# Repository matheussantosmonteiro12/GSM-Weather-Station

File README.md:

# GSM-Weather-Station
Estação meteorológica que mede microclimas e envia esses dados via GSM. 
## Resumo: 
Este projeto propõe uma rede de monitoramento climático utilizando estações meteorológicas autonomas, que transmitem os dados coletados atraves rede GSM (Global System for Mobile Communications), para um Middleware IoT, responsável por fazer a persistencia dos dados e fornecer informações sobre o clima para as diversas aplicações, focadas em ajudar os usuários no planejamento da rotina diária.
## Programas Necessários:
-**IDE arduino**, https://www.arduino.cc/en/Main/Software.

-**Cura Software** ou **Slic3r**.

## Companentes necessários:
- 1 Módulo A6 Gsm/Gprs.

- 1 Arduino mega.

- 1 Módulo sensor de chuva.

- 1 Módulo sensor de luminosidade de luz LDR.

- 1 Sensor de umidade e temperatura DHT 11.

- 1 Atiny 85.

- 1 Regulador de Tensão 7805 5V.

- 1 Relé nec 5V.

- 1 Módulo carregador tp4056.

- 3 Painel Placa Solar 12v 1.50w Carregador Ecologico 9v.

- 1 Modulo Conversor Tensão Dc/dc Step Up.

## Arquitetura da solução proposta:

## Circuito de alimentação:

**1) Relé, 2) Microcontrolador, 3) Carregador de bateria, 4) Regulador de tensão.**

## Circuito principal:

**1) Sensor de gás, 2) Sensor de temperatura e umidade, 3) Sensor de luminosidade, 4) Sensor de chuva, 5) A6 GSM/GPRS, 6) Microcontrolador.**

## Versão final da estação:

#### Link do Artigo sobre esse projeto:
https://ieeexplore.ieee.org/abstract/document/8896242

#### OBS:
Para qualquer outras duvidas me mande um email no matheus.monteiro@uiot.org.

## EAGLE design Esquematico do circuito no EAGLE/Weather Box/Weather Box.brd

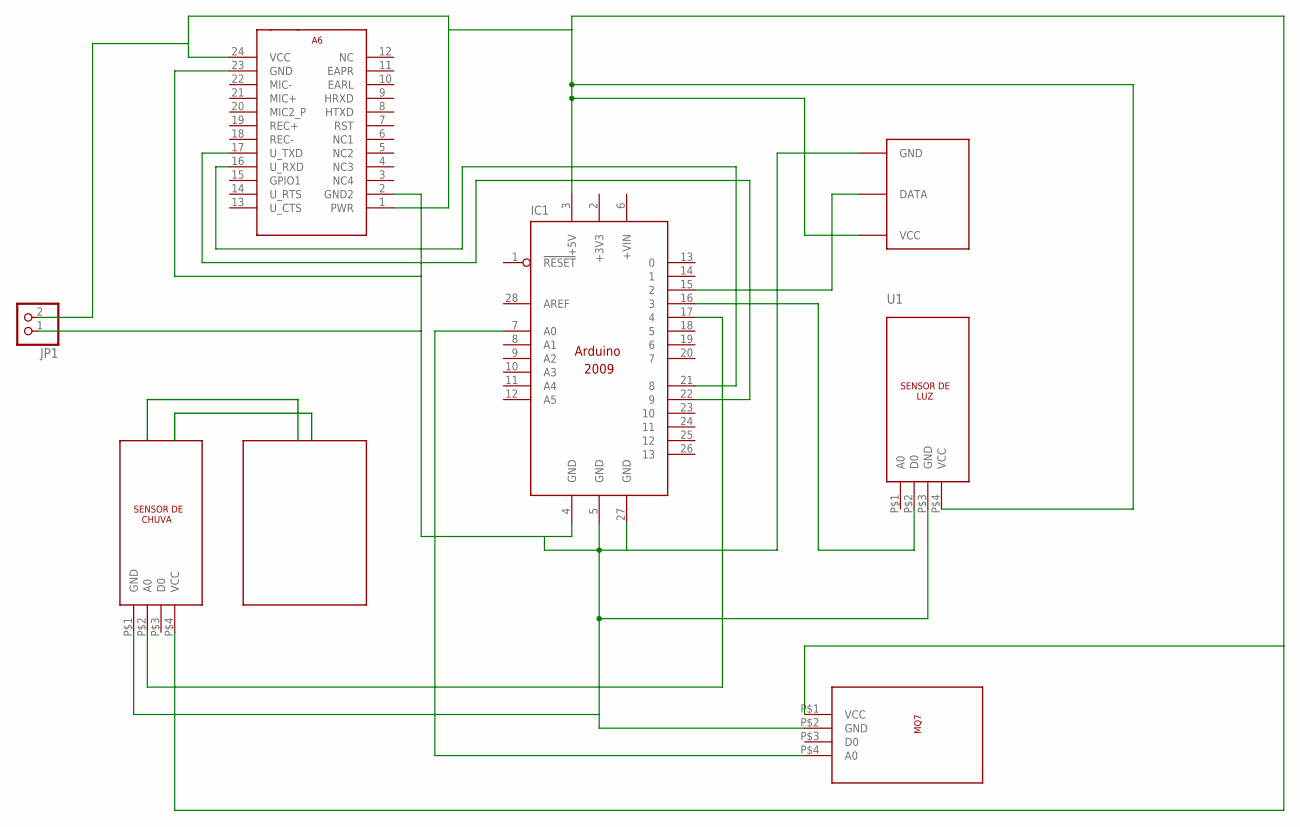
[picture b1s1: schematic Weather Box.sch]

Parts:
IC1: ARDUINO2009_10; ARDUINO2009
JP1: PINHD-1X2; 1X02
SHT1: DHT11DHT11-UPRIGHT; DHT11-UP
U1: LDRLDR-UPRIGHT; LDR-UP
U2: A6GPRS; A6_MODULE_V3
U3: RAINLDR-UPRIGHT; RAIN-UP
U4: MQ7MQ7-UPRIGHT; MQ7-UP

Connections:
+3V3: IC1.2 (+3V3)
unnamed: IC1.7 (A0), U4.P$4 (A0)
unnamed: IC1.3 (+5V), JP1.2, SHT1.P$1 (VCC), U1.P$4 (VCC), U2.1 (PWR), U2.24 (VCC), U3.P$4 (VCC), U4.P$1 (VCC)
unnamed: IC1.22 (9), U2.17 (U_TXD)
unnamed: IC1.21 (8), U2.16 (U_RXD)
unnamed: IC1.4 (GND), IC1.5 (GND), IC1.27 (GND), JP1.1, SHT1.P$4 (GND), U1.P$3 (GND), U2.2 (GND2), U2.23 (GND), U3.P$1 (GND), U4.P$2 (GND)
unnamed: IC1.17 (4), U3.P$2 (A0)
unnamed: IC1.16 (3), U1.P$2 (D0)
unnamed: IC1.15 (2), SHT1.P$3 (DATA)

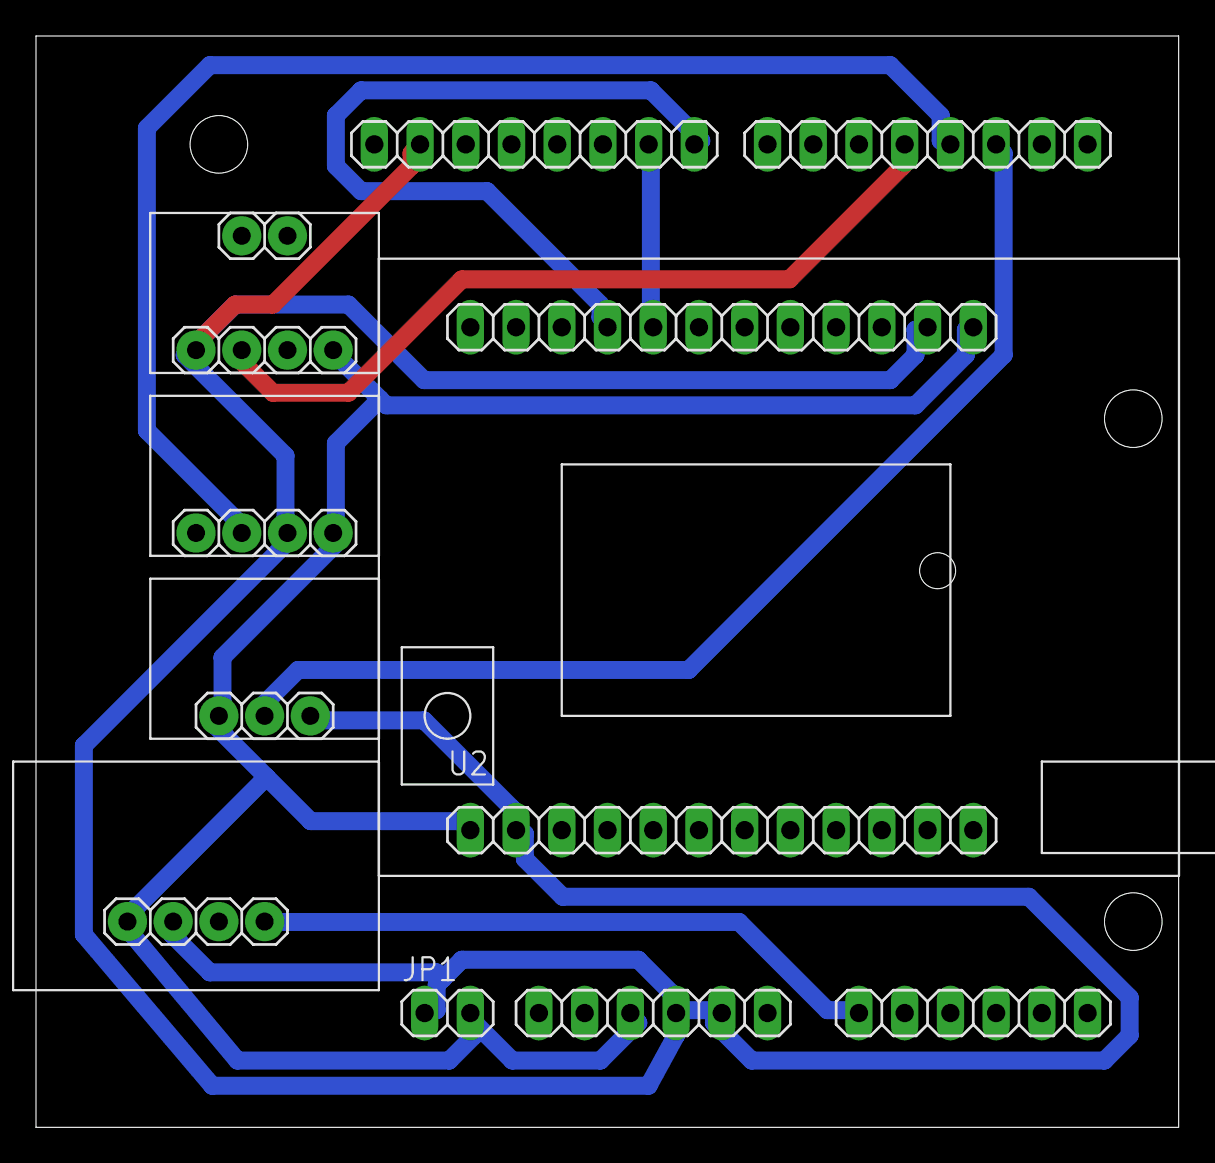
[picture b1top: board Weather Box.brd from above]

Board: 2 copper layers, 63.5 x 60.6 mm, 7 parts (0 on the bottom side), 8 nets.

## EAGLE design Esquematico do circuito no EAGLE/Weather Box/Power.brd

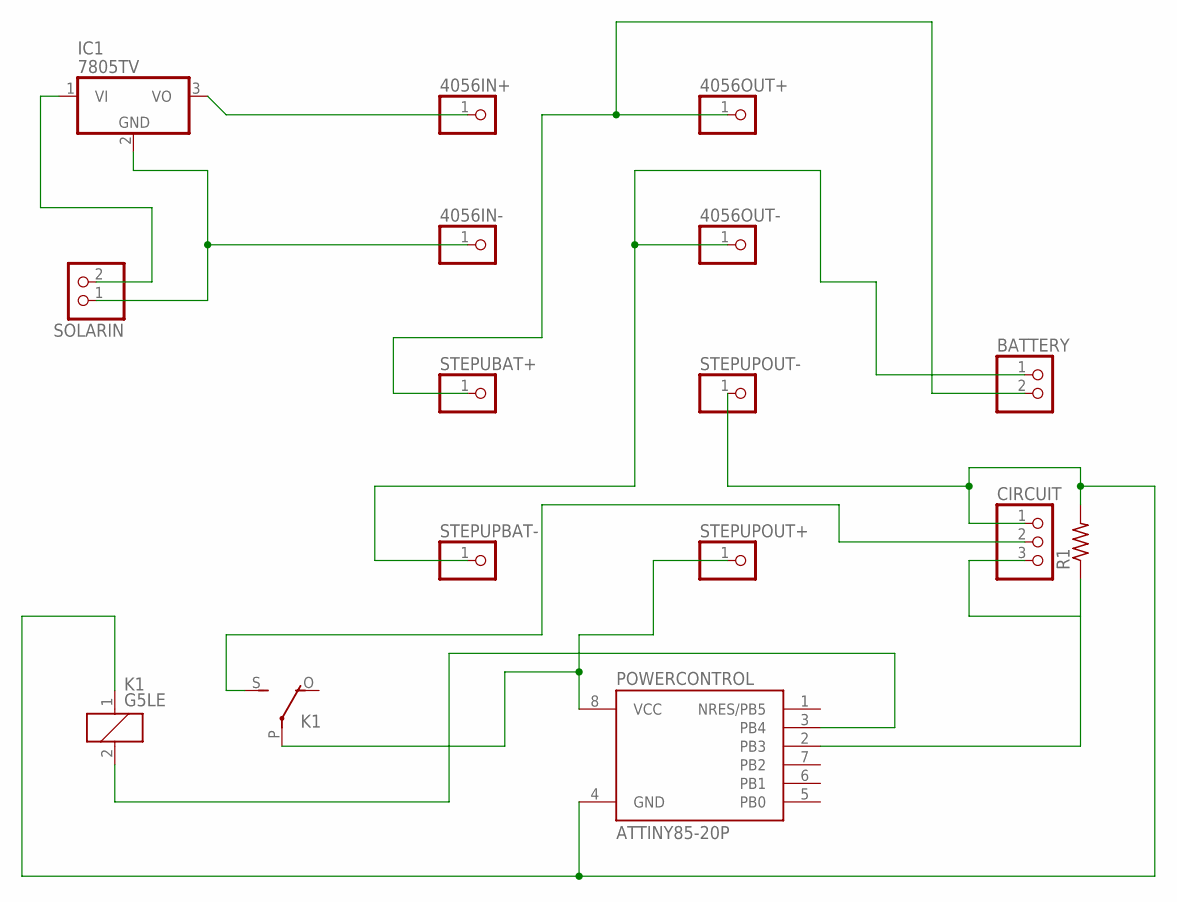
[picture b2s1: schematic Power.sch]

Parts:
4056IN+, 4056IN-, 4056OUT+, 4056OUT-: PINHD-1X1; 1X01
BATTERY: PINHD-1X2; 1X02
CIRCUIT: PINHD-1X3; 1X03
IC1: 7805TV; TO220V
K1: G5LE
POWERCONTROL: ATTINY85-20P; PDIP08_300MIL
R1: R-US_0204/7; 0204/7
SOLARIN: PINHD-1X2; 1X02
STEPUBAT+: PINHD-1X1; 1X01
STEPUPBAT-: PINHD-1X1; 1X01
STEPUPOUT+: PINHD-1X1; 1X01
STEPUPOUT-: PINHD-1X1; 1X01

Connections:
unnamed: IC1.1 (VI), SOLARIN.2
unnamed: 4056IN-.1, IC1.2 (GND), SOLARIN.1
unnamed: 4056IN+.1, IC1.3 (VO)
unnamed: 4056OUT+.1, BATTERY.2, STEPUBAT+.1
unnamed: K1.2, POWERCONTROL.3 (PB4)
unnamed: K1.P, POWERCONTROL.8 (VCC), STEPUPOUT+.1
unnamed: CIRCUIT.2, K1.S
unnamed: CIRCUIT.1, K1.1, POWERCONTROL.4 (GND), R1.2, STEPUPOUT-.1
unnamed: CIRCUIT.3, POWERCONTROL.2 (PB3), R1.1
unnamed: 4056OUT-.1, BATTERY.1, STEPUPBAT-.1

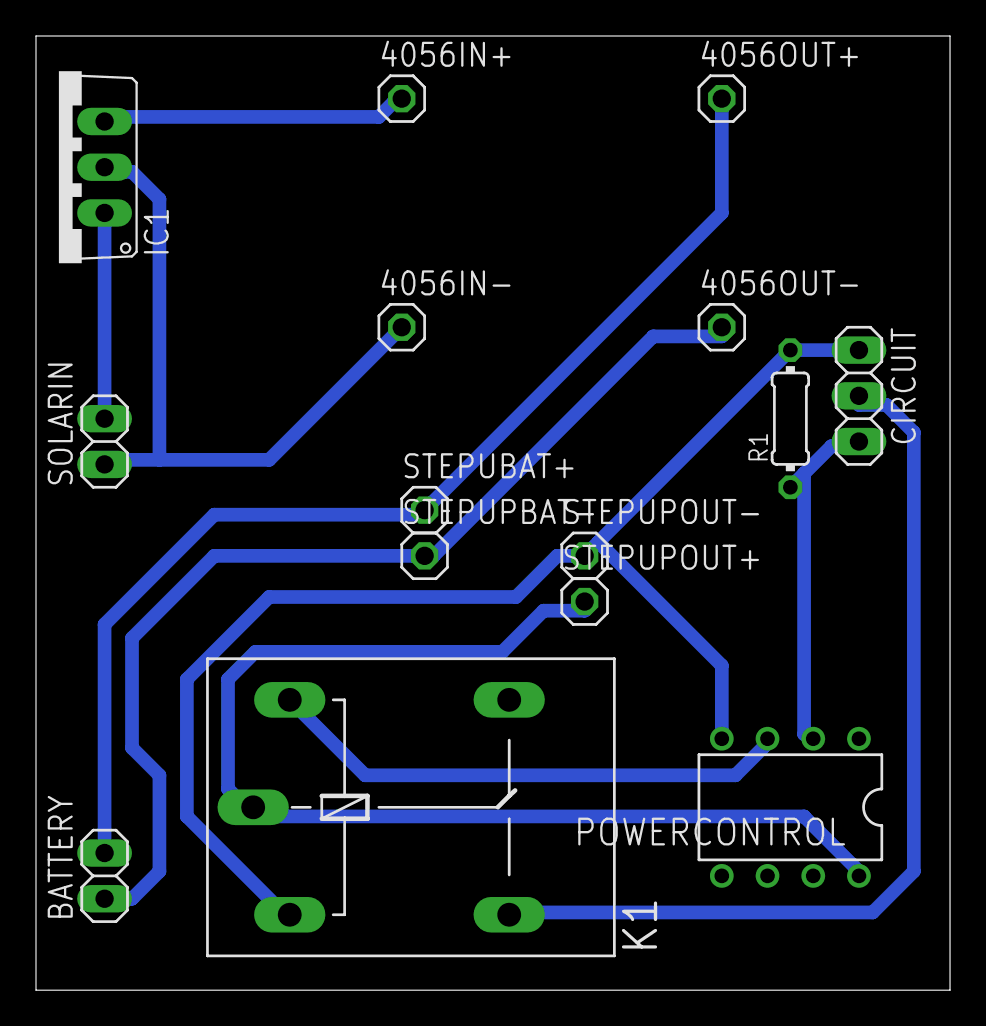
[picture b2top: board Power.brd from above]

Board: 2 copper layers, 50.8 x 53.0 mm, 15 parts (0 on the bottom side), 10 nets.

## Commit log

2020-06-23 Codigo do programa
2020-06-23 Esquematico
2020-06-23 Fotos do Projeto
2020-06-23 Modelo em 3D
2020-06-23 Bibliotecas
2020-06-23 Instrução
    Instruções para impressão
